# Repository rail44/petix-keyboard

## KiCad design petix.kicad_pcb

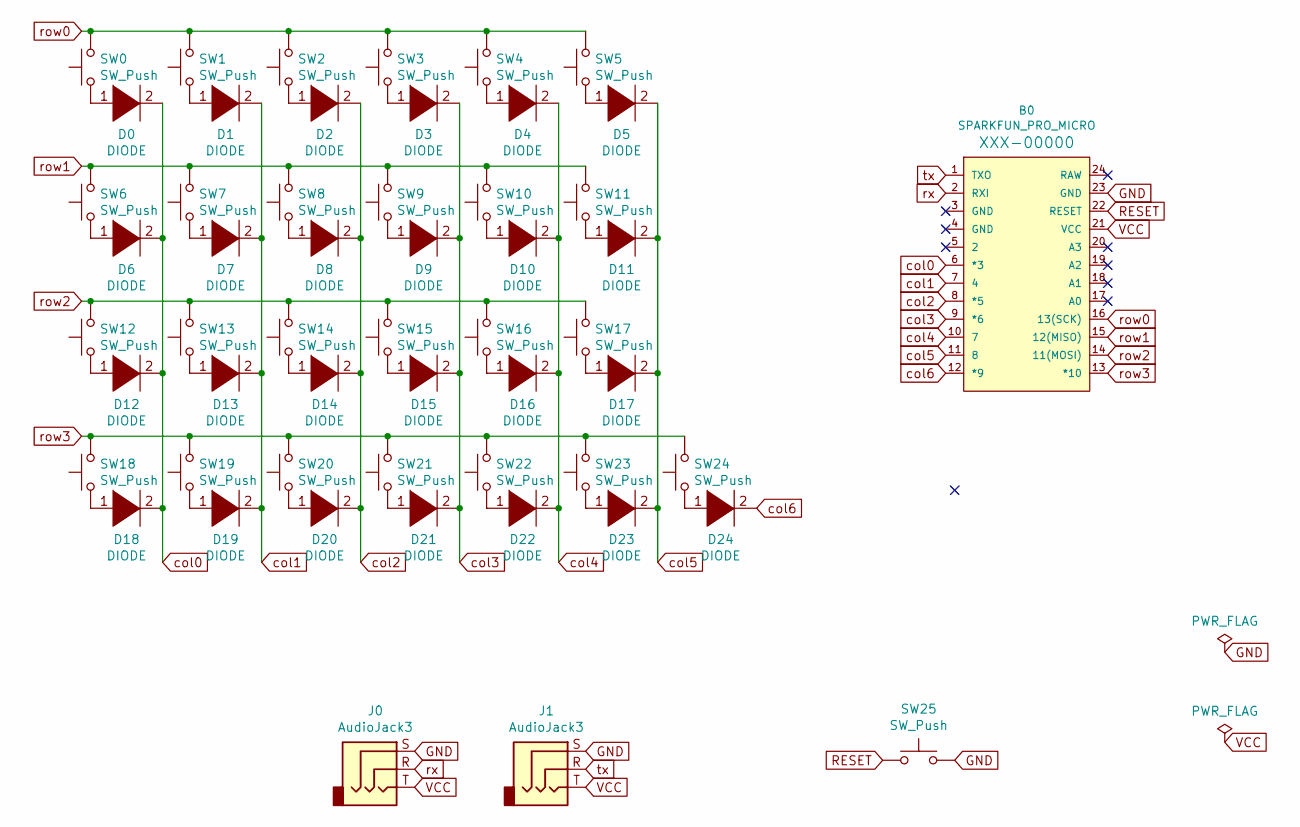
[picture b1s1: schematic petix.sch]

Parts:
B0: SPARKFUN_PRO_MICRO
D0, D1, D2, D3, D4, D5, D6, D7, D8, D9, D10, D11, D12, D13, D14, D15, D16, D17, D18, D19, D20, D21, D22, D23, D24: DIODE; DIODE-1N4148
J0, J1: AudioJack3; Jack_3.5mm_CUI_SJ1-3533NG_Horizontal
SW0, SW1, SW2, SW3, SW4, SW5, SW6, SW7, SW8, SW9, SW10, SW11, SW12, SW13, SW14, SW15, SW16, SW17, SW18, SW19, SW20, SW21, SW22, SW23, SW24: SW_Push; Kailh-PG1425-X-Switch-reversible
SW25: SW_Push; TVBP06B043CWB

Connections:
GND: B0.23 (GND), J0.S, J1.S, SW25.2
unnamed: D0.1 (K), SW0.1
unnamed: D1.1 (K), SW1.1
unnamed: D2.1 (K), SW2.1
unnamed: D3.1 (K), SW3.1
unnamed: D4.1 (K), SW4.1
unnamed: D5.1 (K), SW5.1
unnamed: D6.1 (K), SW6.1
unnamed: D7.1 (K), SW7.1
unnamed: D8.1 (K), SW8.1
unnamed: D9.1 (K), SW9.1
unnamed: D10.1 (K), SW10.1
unnamed: D11.1 (K), SW11.1
unnamed: D12.1 (K), SW12.1
unnamed: D13.1 (K), SW13.1
unnamed: D14.1 (K), SW14.1
unnamed: D15.1 (K), SW15.1
unnamed: D16.1 (K), SW16.1
unnamed: D17.1 (K), SW17.1
unnamed: D18.1 (K), SW18.1
unnamed: D19.1 (K), SW19.1
unnamed: D20.1 (K), SW20.1
unnamed: D21.1 (K), SW21.1
unnamed: D22.1 (K), SW22.1
unnamed: D23.1 (K), SW23.1
unnamed: D24.1 (K), SW24.1
RESET: B0.22 (RESET), SW25.1
VCC: B0.21 (VCC), J0.T, J1.T
col0: B0.6 (*3), D0.2 (A), D6.2 (A), D12.2 (A), D18.2 (A)
col1: B0.7 (4), D1.2 (A), D7.2 (A), D13.2 (A), D19.2 (A)
col2: B0.8 (*5), D2.2 (A), D8.2 (A), D14.2 (A), D20.2 (A)
col3: B0.9 (*6), D3.2 (A), D9.2 (A), D15.2 (A), D21.2 (A)
col4: B0.10 (7), D4.2 (A), D10.2 (A), D16.2 (A), D22.2 (A)
col5: B0.11 (8), D5.2 (A), D11.2 (A), D17.2 (A), D23.2 (A)
col6: B0.12 (*9), D24.2 (A)
row0: B0.16 (13(SCK)), SW0.2, SW1.2, SW2.2, SW3.2, SW4.2, SW5.2
row1: B0.15 (12(MISO)), SW6.2, SW7.2, SW8.2, SW9.2, SW10.2, SW11.2
row2: B0.14 (11(MOSI)), SW12.2, SW13.2, SW14.2, SW15.2, SW16.2, SW17.2
row3: B0.13 (*10), SW18.2, SW19.2, SW20.2, SW21.2, SW22.2, SW23.2, SW24.2
rx: B0.2 (RXI), J0.R
tx: B0.1 (TXO), J1.R

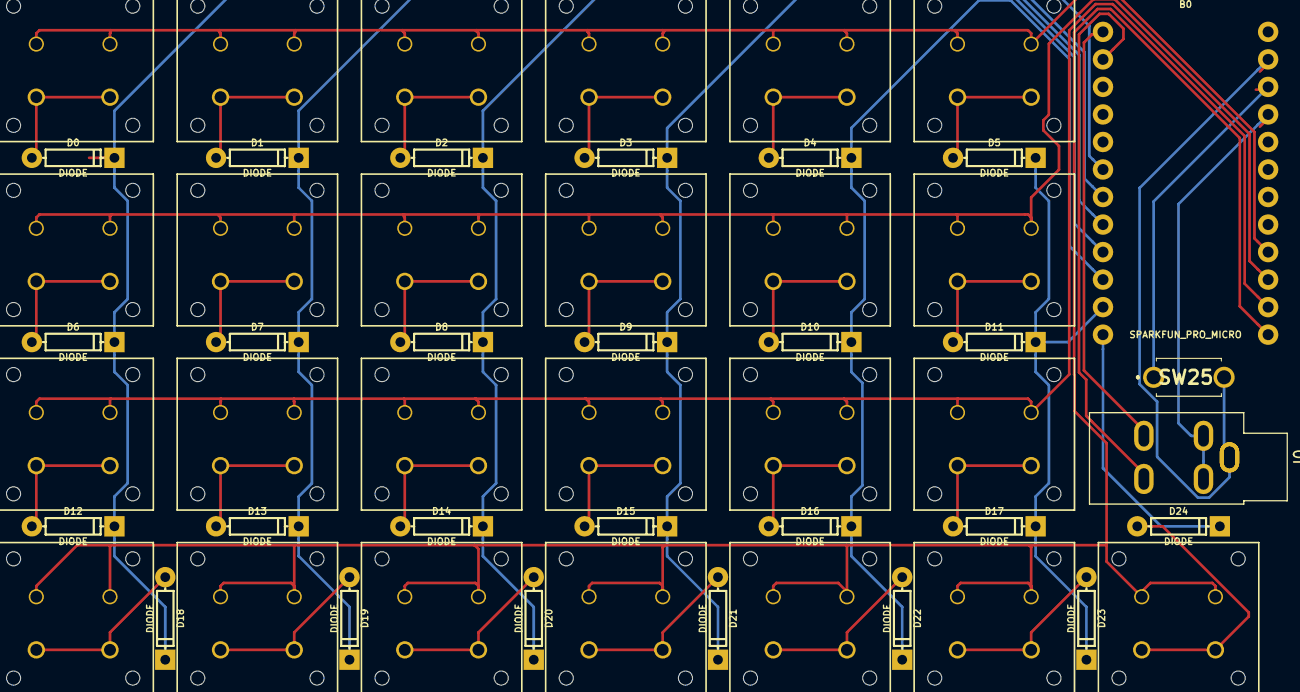
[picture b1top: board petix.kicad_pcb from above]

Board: 2 copper layers, 54 parts (1 on the bottom side), 41 nets.
